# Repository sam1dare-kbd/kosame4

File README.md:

# kosame4 小雨4

## What is kosame4？

キーキャップディスプレイ用マクロパッドです。
アルチザンキーキャップや透明のキーキャップを飾るために設計しました。

Macro pad for keycap display.
Designed to decorate artisan keycaps and transparent keycaps.

<br>
<br>

## Build Guide  
https://note.com/sam1dare/n/n9370afc2b88c
(Japanese text only.)  

<br>

## License  
このプロジェクトは MITライセンスに基づいてライセンスされています。詳細については、LICENSE.txt ファイルを参照してください。  
This project is licensed under the MIT License, see the LICENSE.txt file for details.

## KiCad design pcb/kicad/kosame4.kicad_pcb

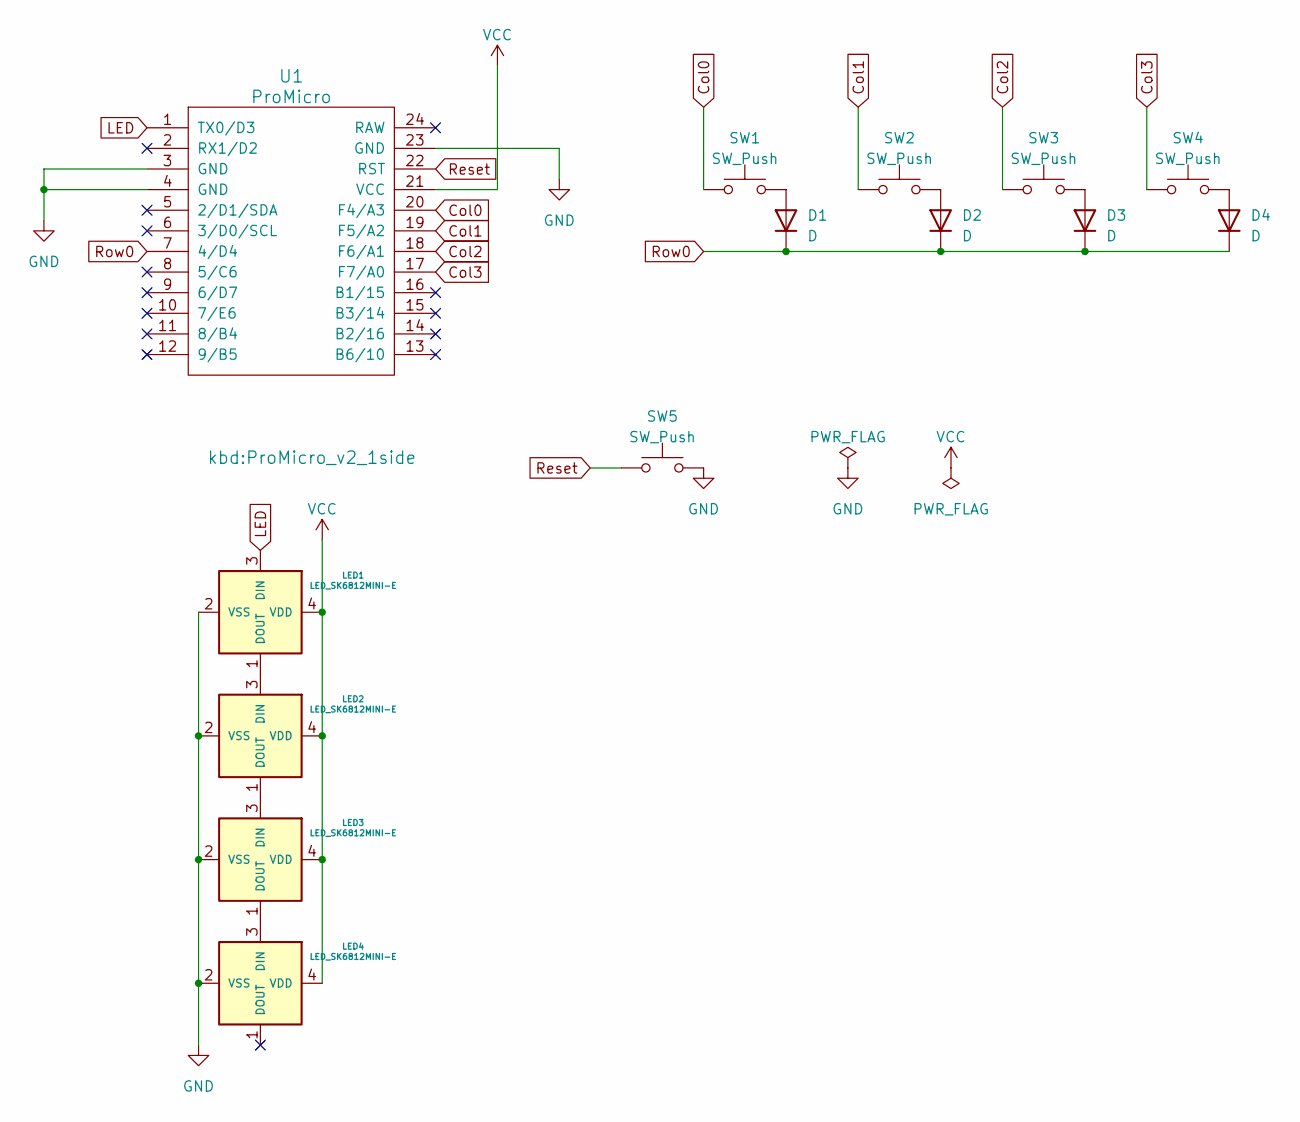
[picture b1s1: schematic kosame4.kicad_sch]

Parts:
D1, D2, D3, D4: D; Diode_TH_SMD
LED1, LED2, LED3, LED4: LED_SK6812MINI-E; LED_SK6812MINI-E_BL
SW1, SW2, SW3, SW4: SW_Push; CherryMX_Hotswap
SW5: SW_Push; ResetSW_1side
U1: ProMicro; ProMicro_v2_1side

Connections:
Col0: SW1.1, U1.20 (F4/A3)
Col1: SW2.1, U1.19 (F5/A2)
Col2: SW3.1, U1.18 (F6/A1)
Col3: SW4.1, U1.17 (F7/A0)
GND: LED1.2 (VSS), LED2.2 (VSS), LED3.2 (VSS), LED4.2 (VSS), SW5.2, U1.3 (GND), U1.4 (GND), U1.23 (GND)
LED: LED1.3 (DIN), U1.1 (TX0/D3)
unnamed: D1.2 (A), SW1.2
unnamed: D2.2 (A), SW2.2
unnamed: D3.2 (A), SW3.2
unnamed: D4.2 (A), SW4.2
unnamed: LED1.1 (DOUT), LED2.3 (DIN)
unnamed: LED2.1 (DOUT), LED3.3 (DIN)
unnamed: LED3.1 (DOUT), LED4.3 (DIN)
Reset: SW5.1, U1.22 (RST)
Row0: D1.1 (K), D2.1 (K), D3.1 (K), D4.1 (K), U1.7 (4/D4)
VCC: LED1.4 (VDD), LED2.4 (VDD), LED3.4 (VDD), LED4.4 (VDD), U1.21 (VCC)

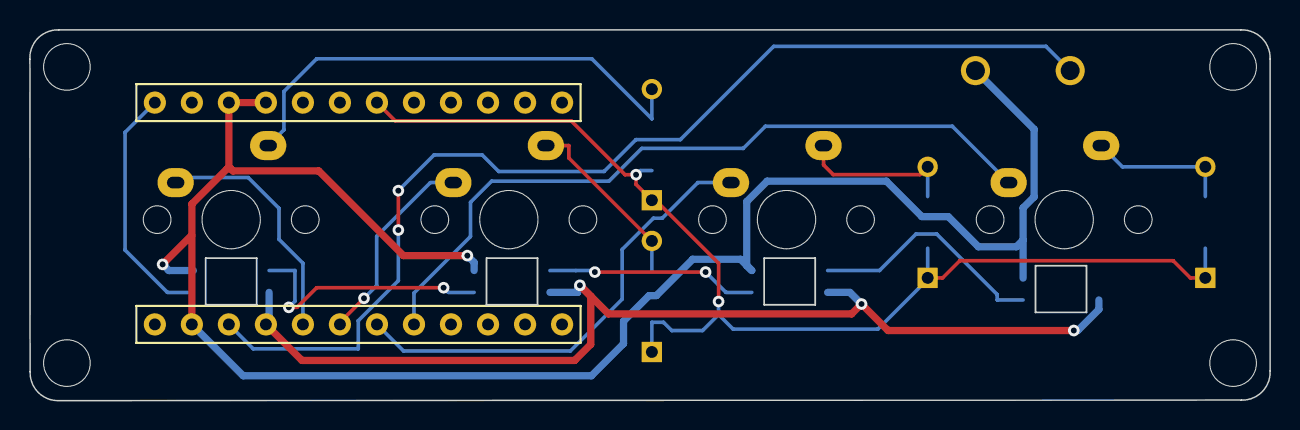
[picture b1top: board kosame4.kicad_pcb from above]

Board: 2 copper layers, 85.1 x 25.4 mm, 18 parts (1 on the bottom side), 16 nets.

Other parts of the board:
Ref00, Ref01, Ref02, Ref03: Val**; m3_Screw_Hole_EdgeCuts

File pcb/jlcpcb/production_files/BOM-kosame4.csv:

Comment,Designator,Footprint,LCSC
LED_SK6812MINI-E,LED2,LED_SK6812MINI-E_BL,
SW_Push,SW1,CherryMX_1u,
D,D1,Diode_TH_SMD,
ProMicro,U1,ProMicro_v2_1side,
LED_SK6812MINI-E,LED4,LED_SK6812MINI-E_BL,
LED_SK6812MINI-E,LED1,LED_SK6812MINI-E_BL,
LED_SK6812MINI-E,LED3,LED_SK6812MINI-E_BL,
SW_Push,SW2,CherryMX_1u,
SW_Push,SW3,CherryMX_1u,
D,D4,Diode_TH_SMD,
D,D2,Diode_TH_SMD,
D,D3,Diode_TH_SMD,
SW_Push,SW4,CherryMX_1u,
SW_Push,SW5,ResetSW_1side,

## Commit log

2023-08-22 Create LICENSE
2024-09-05 Update LICENSE
